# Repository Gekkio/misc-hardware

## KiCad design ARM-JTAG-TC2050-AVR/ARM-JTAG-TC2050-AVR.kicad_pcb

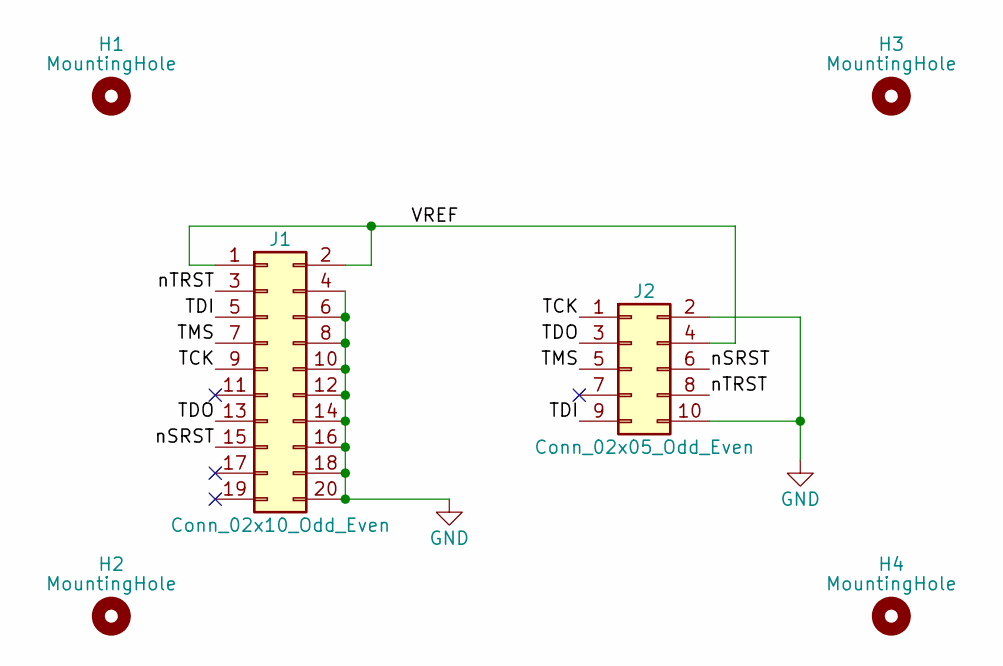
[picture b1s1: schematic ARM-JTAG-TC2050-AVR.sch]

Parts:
H1, H2, H3, H4: MountingHole; MountingHole_3.2mm_M3
J1: Conn_02x10_Odd_Even; IDC-Header_2x10_P2.54mm_Vertical
J2: Conn_02x05_Odd_Even; IDC-Header_2x05_P2.54mm_Vertical

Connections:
/TCK: J1.9, J2.1
/TDI: J1.5, J2.9
/TDO: J1.13, J2.3
/TMS: J1.7, J2.5
/VREF: J1.1, J1.2, J2.4
/nSRST: J1.15, J2.6
/nTRST: J1.3, J2.8
GND: J1.4, J1.6, J1.8, J1.10, J1.12, J1.14, J1.16, J1.18, J1.20, J2.2, J2.10

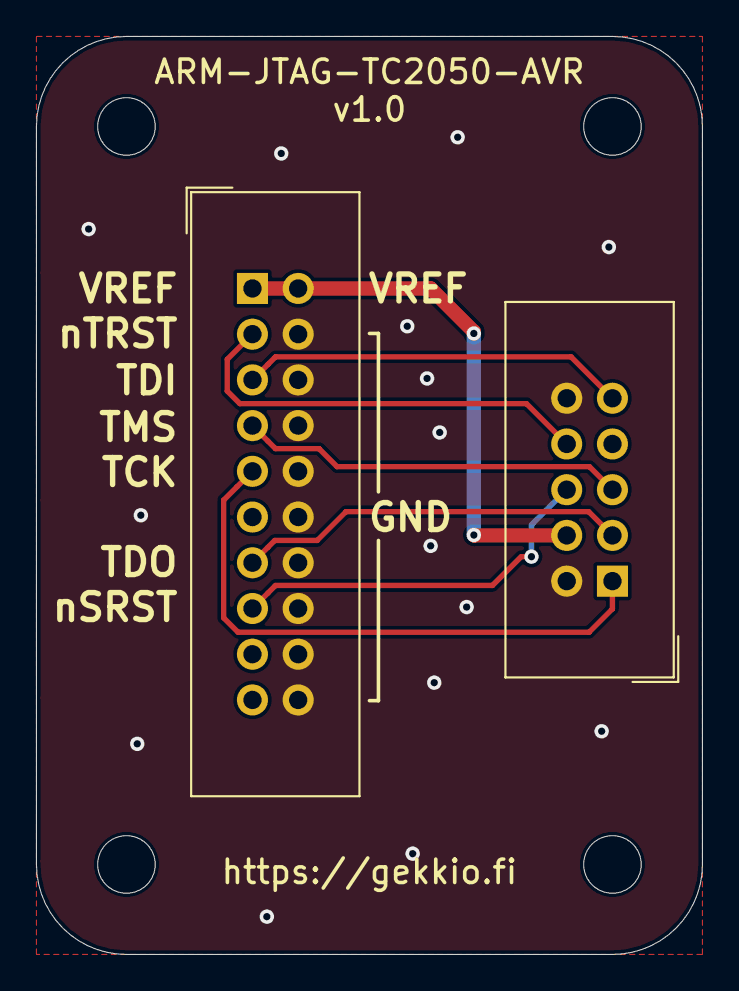
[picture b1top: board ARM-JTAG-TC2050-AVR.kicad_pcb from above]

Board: 2 copper layers, 37.0 x 51.0 mm, 6 parts (0 on the bottom side), 8 nets.

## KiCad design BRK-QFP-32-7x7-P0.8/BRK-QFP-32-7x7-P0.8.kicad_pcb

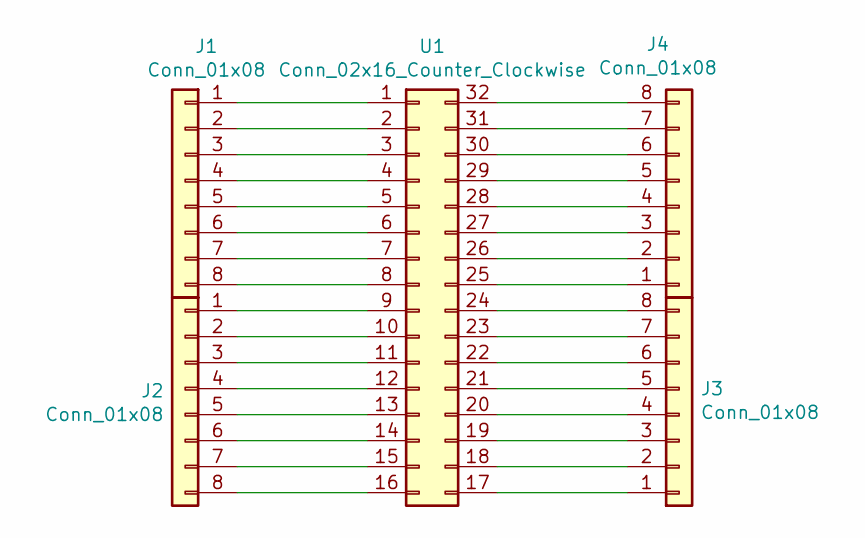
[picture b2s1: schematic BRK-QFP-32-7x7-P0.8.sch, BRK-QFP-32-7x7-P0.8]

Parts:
J1, J2, J3, J4: Conn_01x08; PinHeader_1x08_P2.54mm_Vertical
U1: Conn_02x16_Counter_Clockwise; TQFP-32_7x7mm_P0.8mm

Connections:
unnamed: J1.1, U1.1
unnamed: J1.2, U1.2
unnamed: J1.3, U1.3
unnamed: J1.4, U1.4
unnamed: J1.5, U1.5
unnamed: J1.6, U1.6
unnamed: J1.7, U1.7
unnamed: J1.8, U1.8
unnamed: J2.1, U1.9
unnamed: J2.2, U1.10
unnamed: J2.3, U1.11
unnamed: J2.4, U1.12
unnamed: J2.5, U1.13
unnamed: J2.6, U1.14
unnamed: J2.7, U1.15
unnamed: J2.8, U1.16
unnamed: J3.1, U1.17
unnamed: J3.2, U1.18
unnamed: J3.3, U1.19
unnamed: J3.4, U1.20
unnamed: J3.5, U1.21
unnamed: J3.6, U1.22
unnamed: J3.7, U1.23
unnamed: J3.8, U1.24
unnamed: J4.1, U1.25
unnamed: J4.2, U1.26
unnamed: J4.3, U1.27
unnamed: J4.4, U1.28
unnamed: J4.5, U1.29
unnamed: J4.6, U1.30
unnamed: J4.7, U1.31
unnamed: J4.8, U1.32

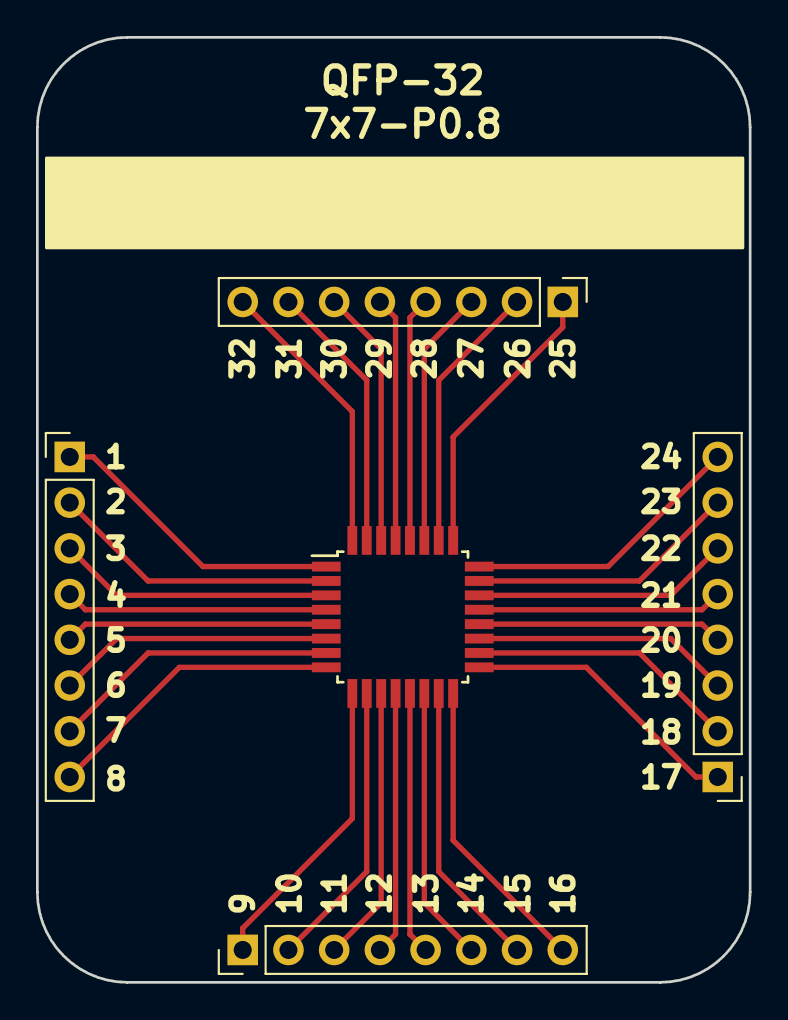
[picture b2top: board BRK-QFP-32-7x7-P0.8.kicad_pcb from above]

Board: 2 copper layers, 39.6 x 52.5 mm, 5 parts (0 on the bottom side), 32 nets.

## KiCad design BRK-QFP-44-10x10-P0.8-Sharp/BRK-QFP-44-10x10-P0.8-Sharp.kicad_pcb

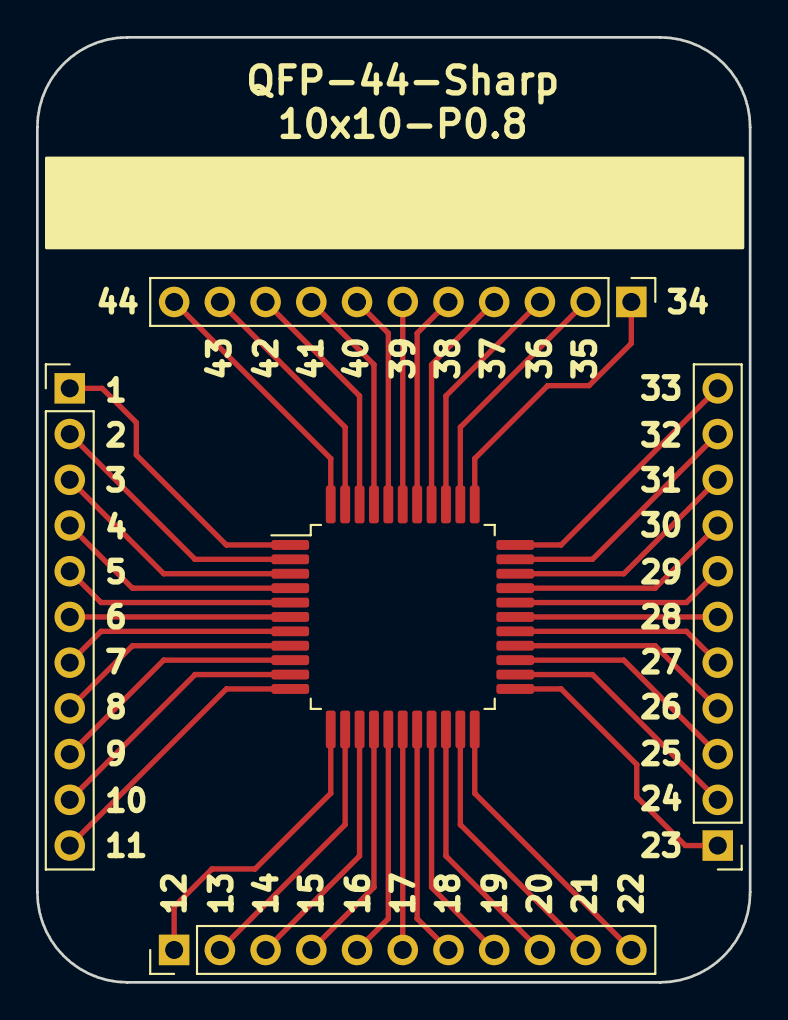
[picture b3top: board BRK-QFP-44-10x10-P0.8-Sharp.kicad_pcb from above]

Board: 2 copper layers, 39.6 x 52.5 mm, 5 parts (0 on the bottom side), 44 nets.

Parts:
J1, J2, J3, J4: Conn_01x11; PinHeader_1x11_P2.54mm_Vertical
U1: Conn_02x22_Counter_Clockwise; Sharp_QFP-44_10x10mm_P0.8mm

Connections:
unnamed: J1.1, U1.1
unnamed: J1.2, U1.2
unnamed: J1.3, U1.3
unnamed: J1.4, U1.4
unnamed: J1.5, U1.5
unnamed: J1.6, U1.6
unnamed: J1.7, U1.7
unnamed: J1.8, U1.8
unnamed: J1.9, U1.9
unnamed: J1.10, U1.10
unnamed: J1.11, U1.11
unnamed: J2.1, U1.12
unnamed: J2.2, U1.13
unnamed: J2.3, U1.14
unnamed: J2.4, U1.15
unnamed: J2.5, U1.16
unnamed: J2.6, U1.17
unnamed: J2.7, U1.18
unnamed: J2.8, U1.19
unnamed: J2.9, U1.20
unnamed: J2.10, U1.21
unnamed: J2.11, U1.22
unnamed: J3.1, U1.23
unnamed: J3.2, U1.24
unnamed: J3.3, U1.25
unnamed: J3.4, U1.26
unnamed: J3.5, U1.27
unnamed: J3.6, U1.28
unnamed: J3.7, U1.29
unnamed: J3.8, U1.30
unnamed: J3.9, U1.31
unnamed: J3.10, U1.32
unnamed: J3.11, U1.33
unnamed: J4.1, U1.34
unnamed: J4.2, U1.35
unnamed: J4.3, U1.36
unnamed: J4.4, U1.37
unnamed: J4.5, U1.38
unnamed: J4.6, U1.39
unnamed: J4.7, U1.40
unnamed: J4.8, U1.41
unnamed: J4.9, U1.42
unnamed: J4.10, U1.43
unnamed: J4.11, U1.44

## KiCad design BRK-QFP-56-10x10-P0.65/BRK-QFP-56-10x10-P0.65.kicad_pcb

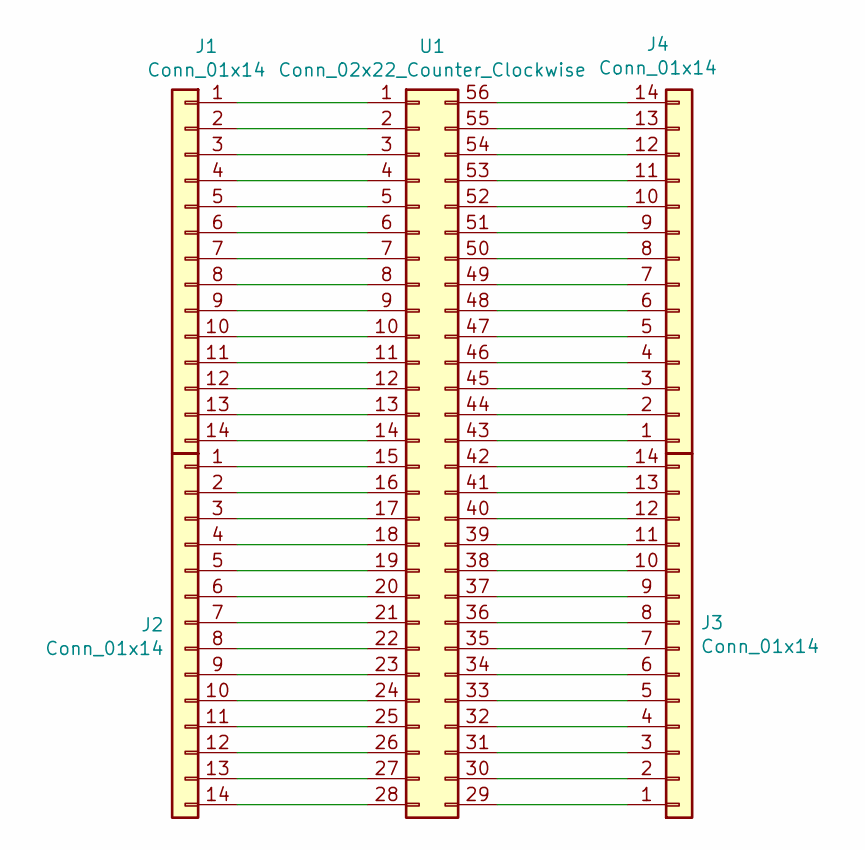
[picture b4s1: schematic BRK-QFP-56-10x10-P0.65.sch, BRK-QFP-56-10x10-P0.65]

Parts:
J1, J2, J3, J4: Conn_01x14; PinHeader_1x14_P2.54mm_Vertical
U1: Conn_02x22_Counter_Clockwise; Rohm_QFP-56_10x10mm_P0.65mm

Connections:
unnamed: J1.1, U1.1
unnamed: J1.2, U1.2
unnamed: J1.3, U1.3
unnamed: J1.4, U1.4
unnamed: J1.5, U1.5
unnamed: J1.6, U1.6
unnamed: J1.7, U1.7
unnamed: J1.8, U1.8
unnamed: J1.9, U1.9
unnamed: J1.10, U1.10
unnamed: J1.11, U1.11
unnamed: J1.12, U1.12
unnamed: J1.13, U1.13
unnamed: J1.14, U1.14
unnamed: J2.1, U1.15
unnamed: J2.2, U1.16
unnamed: J2.3, U1.17
unnamed: J2.4, U1.18
unnamed: J2.5, U1.19
unnamed: J2.6, U1.20
unnamed: J2.7, U1.21
unnamed: J2.8, U1.22
unnamed: J2.9, U1.23
unnamed: J2.10, U1.24
unnamed: J2.11, U1.25
unnamed: J2.12, U1.26
unnamed: J2.13, U1.27
unnamed: J2.14, U1.28
unnamed: J3.1, U1.29
unnamed: J3.2, U1.30
unnamed: J3.3, U1.31
unnamed: J3.4, U1.32
unnamed: J3.5, U1.33
unnamed: J3.6, U1.34
unnamed: J3.7, U1.35
unnamed: J3.8, U1.36
unnamed: J3.9, U1.37
unnamed: J3.10, U1.38
unnamed: J3.11, U1.39
unnamed: J3.12, U1.40
unnamed: J3.13, U1.41
unnamed: J3.14, U1.42
unnamed: J4.1, U1.43
unnamed: J4.2, U1.44
unnamed: J4.3, U1.45
unnamed: J4.4, U1.46
unnamed: J4.5, U1.47
unnamed: J4.6, U1.48
unnamed: J4.7, U1.49
unnamed: J4.8, U1.50
unnamed: J4.9, U1.51
unnamed: J4.10, U1.52
unnamed: J4.11, U1.53
unnamed: J4.12, U1.54
unnamed: J4.13, U1.55
unnamed: J4.14, U1.56

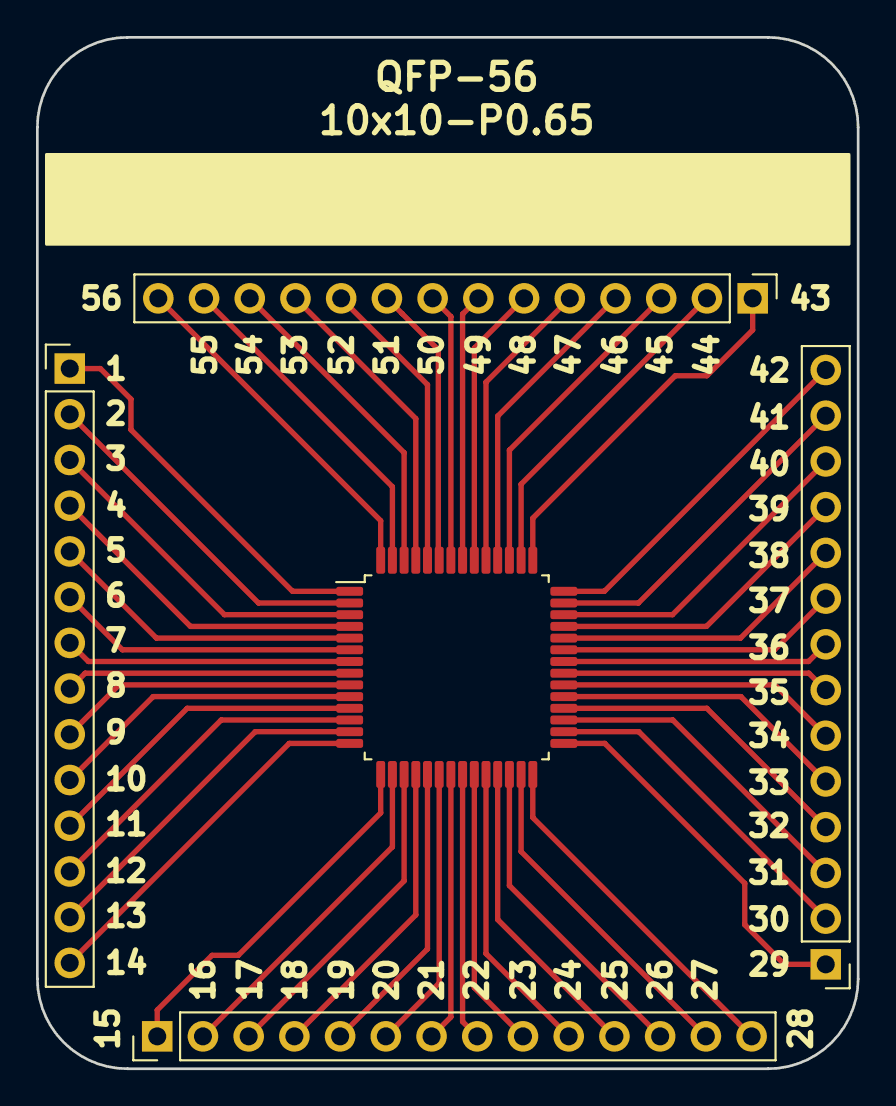
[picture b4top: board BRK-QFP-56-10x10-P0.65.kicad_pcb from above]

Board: 2 copper layers, 45.6 x 57.3 mm, 5 parts (0 on the bottom side), 56 nets.

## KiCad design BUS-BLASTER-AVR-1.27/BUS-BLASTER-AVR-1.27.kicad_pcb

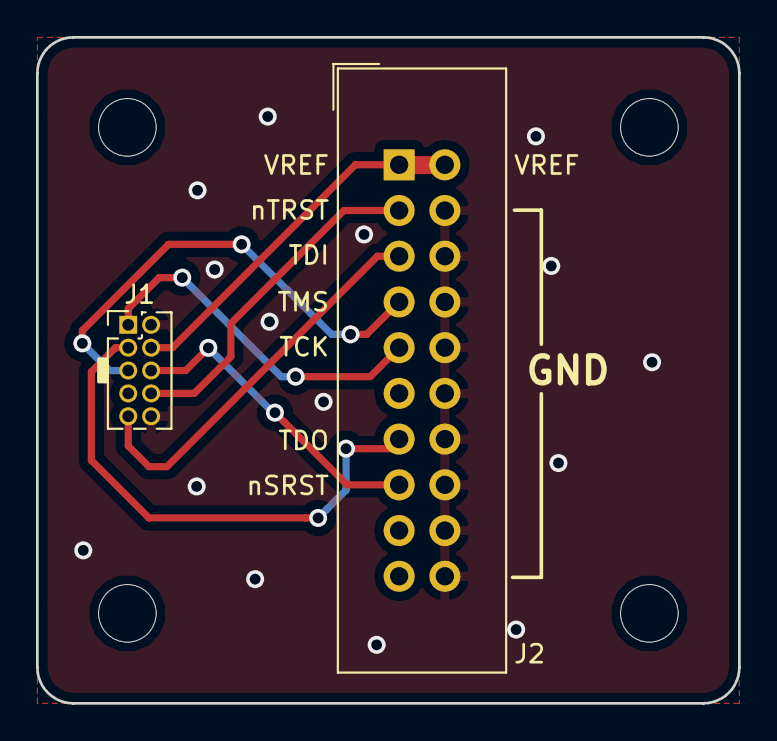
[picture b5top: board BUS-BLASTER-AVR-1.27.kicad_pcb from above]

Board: 2 copper layers, 39.0 x 37.0 mm, 6 parts (0 on the bottom side), 8 nets.

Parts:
H1, H2, H3, H4: MountingHole; MountingHole_3.2mm_M3
J1: Conn_02x05_Odd_Even; PinHeader_2x05_P1.27mm_Vertical
J2: Conn_02x10_Odd_Even; IDC-Header_2x10_P2.54mm_Vertical

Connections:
GND: J1.2, J1.10, J2.4, J2.6, J2.8, J2.10, J2.12, J2.14, J2.16, J2.18, J2.20
TCK: J1.1, J2.9
TDI: J1.9, J2.5
TDO: J1.3, J2.13
TMS: J1.5, J2.7
VREF: J1.4, J2.1, J2.2
nSRST: J1.6, J2.15
nTRST: J1.8, J2.3

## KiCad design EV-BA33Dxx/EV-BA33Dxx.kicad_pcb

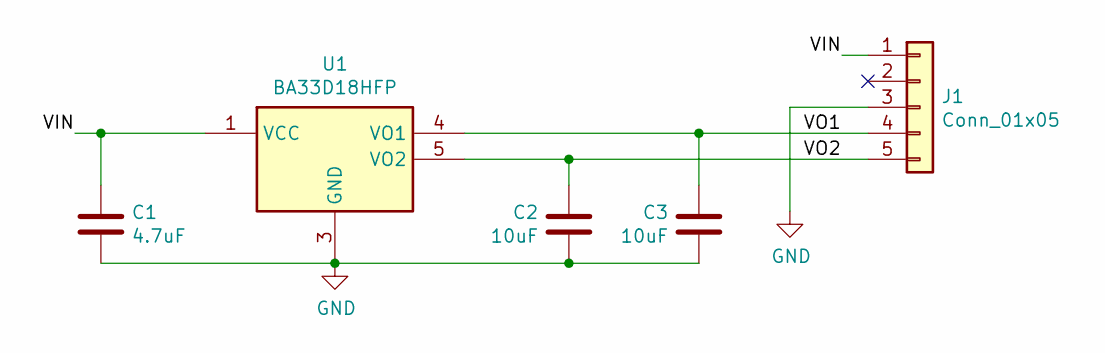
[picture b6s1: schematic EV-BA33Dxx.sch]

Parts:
C1: 4.7uF; C_1206_3216Metric_Pad1.42x1.75mm_HandSolder
C2, C3: 10uF; C_1210_3225Metric_Pad1.42x2.65mm_HandSolder
J1: Conn_01x05; PinHeader_1x05_P2.54mm_Vertical
U1: BA33D18HFP; Rohm_HRP5

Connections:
/VIN: C1.1, J1.1, U1.1 (VCC)
/VO1: C3.1, J1.4, U1.4 (VO1)
/VO2: C2.1, J1.5, U1.5 (VO2)
GND: C1.2, C2.2, C3.2, J1.3, U1.3 (GND)

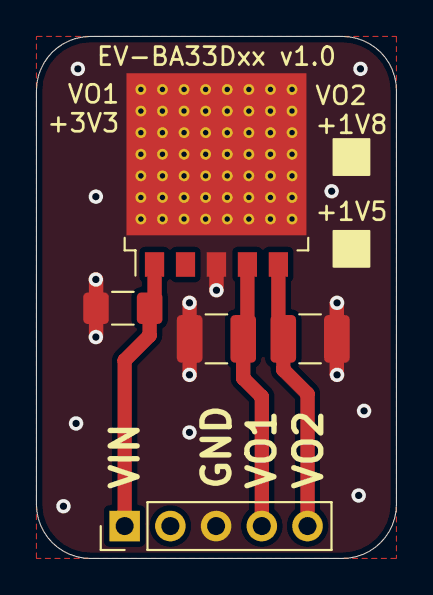
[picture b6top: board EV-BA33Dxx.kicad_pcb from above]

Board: 2 copper layers, 20.0 x 29.0 mm, 5 parts (0 on the bottom side), 4 nets.
